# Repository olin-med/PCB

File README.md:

# PCB baseada em uma Raspberry Pi Pico W

Este arquivo contem os arquivos relativos a uma PCB desenvolvida no KICAD.

## Visão Geral do Projeto

Este projeto envolve a criação de uma PCB que suporta um Raspberry Pi Pico W utilizando um conector específico. A placa incorpora diversos elementos:

- Um módulo de potência que inclui um relé e um transistor, permitindo o manejo de aparelhos de alta potência por meio de uma saída dupla.
- Um LED, que está em série com um resistor de 10k conectado ao Raspberry Pi Pico.

## Autor

Desenvolvido por Ólin Costa

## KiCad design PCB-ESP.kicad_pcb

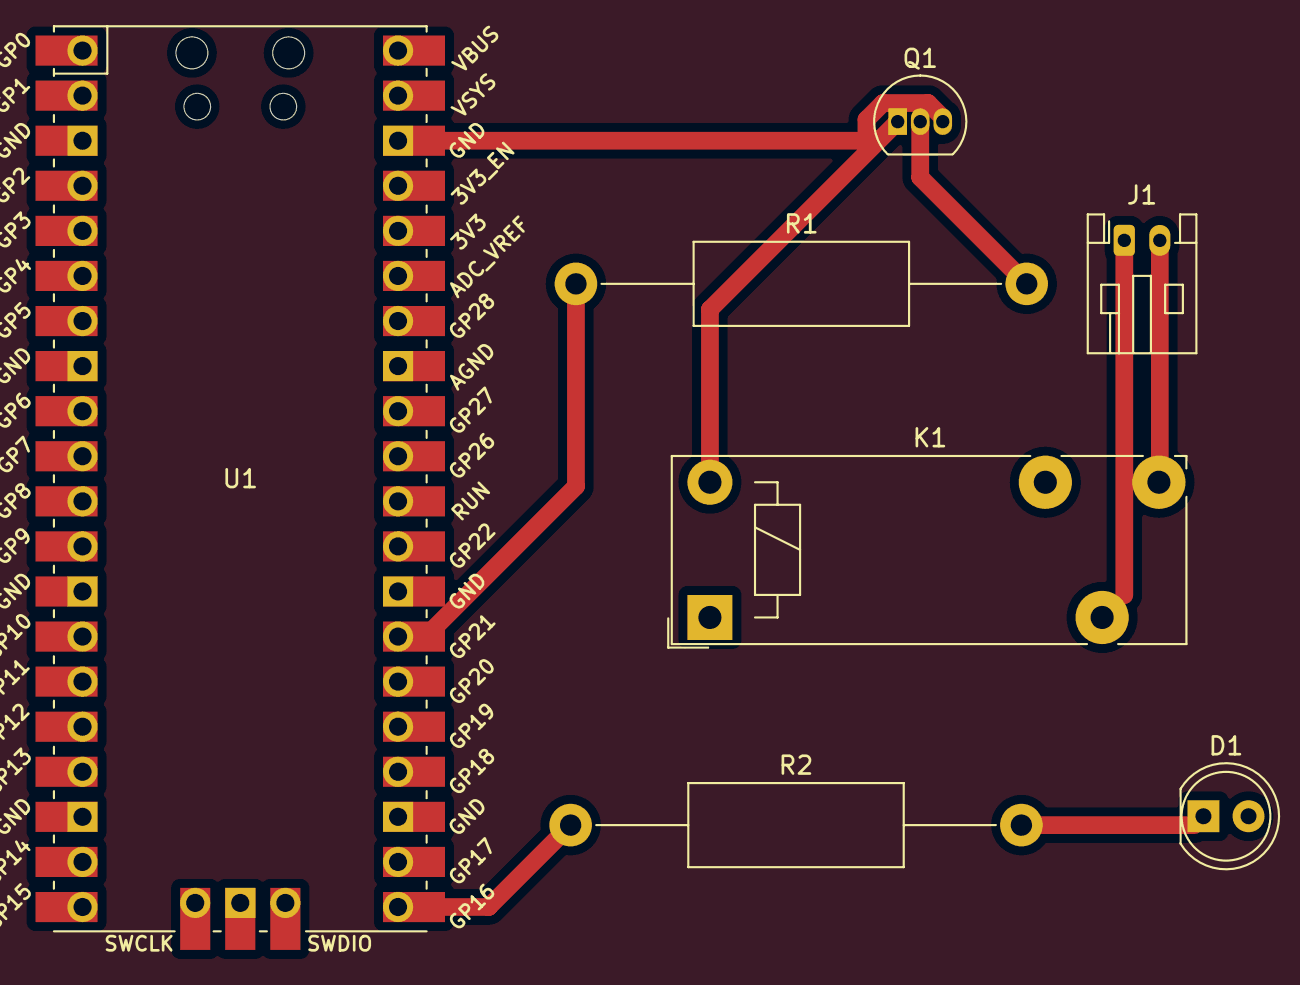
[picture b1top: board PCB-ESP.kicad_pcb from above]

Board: 2 copper layers, 7 parts (0 on the bottom side), 5 nets.

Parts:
D1: LED; LED_D5.0mm_Clear
J1: Conn_01x02_Pin; JST_PH_S2B-PH-K_1x02_P2.00mm_Horizontal
K1: Relay_SPDT; Relay_1-Form-C_Schrack-RYII_RM3.2mm
Q1: BC548; TO-92_Inline
R1, R2: R 10K; R_Axial_DIN0414_L11.9mm_D4.5mm_P25.40mm_Horizontal
U1: Pico; RPi_Pico_SMD_TH

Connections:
GND: K1.A2, Q1.1 (C), Q1.2 (B), Q1.3 (E), R1.2, U1.38 (GND)
GP16: R2.1, U1.21 (GPIO16)
GP21: R1.1, U1.27 (GPIO21), U1.28 (GND)
unnamed: D1.1 (K), R2.2
unnamed: J1.1, J1.2, K1.11, K1.14

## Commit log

2024-04-01 commit da felicidade
